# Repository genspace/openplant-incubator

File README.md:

# OpenPlant Incubator

The code in this repository is open sourced and provides tools to develop a plant incubator.We hope this repository can be used as a model to inspire similar work among other research teams.

ToDo: Update this https://trello.com/b/W0jccEJs/welcome-to-the-project

Complete block diagram is saved in the genspace/openplant google drive. See `Incubator functional block diagram`

Please feel free to get in touch with the team.

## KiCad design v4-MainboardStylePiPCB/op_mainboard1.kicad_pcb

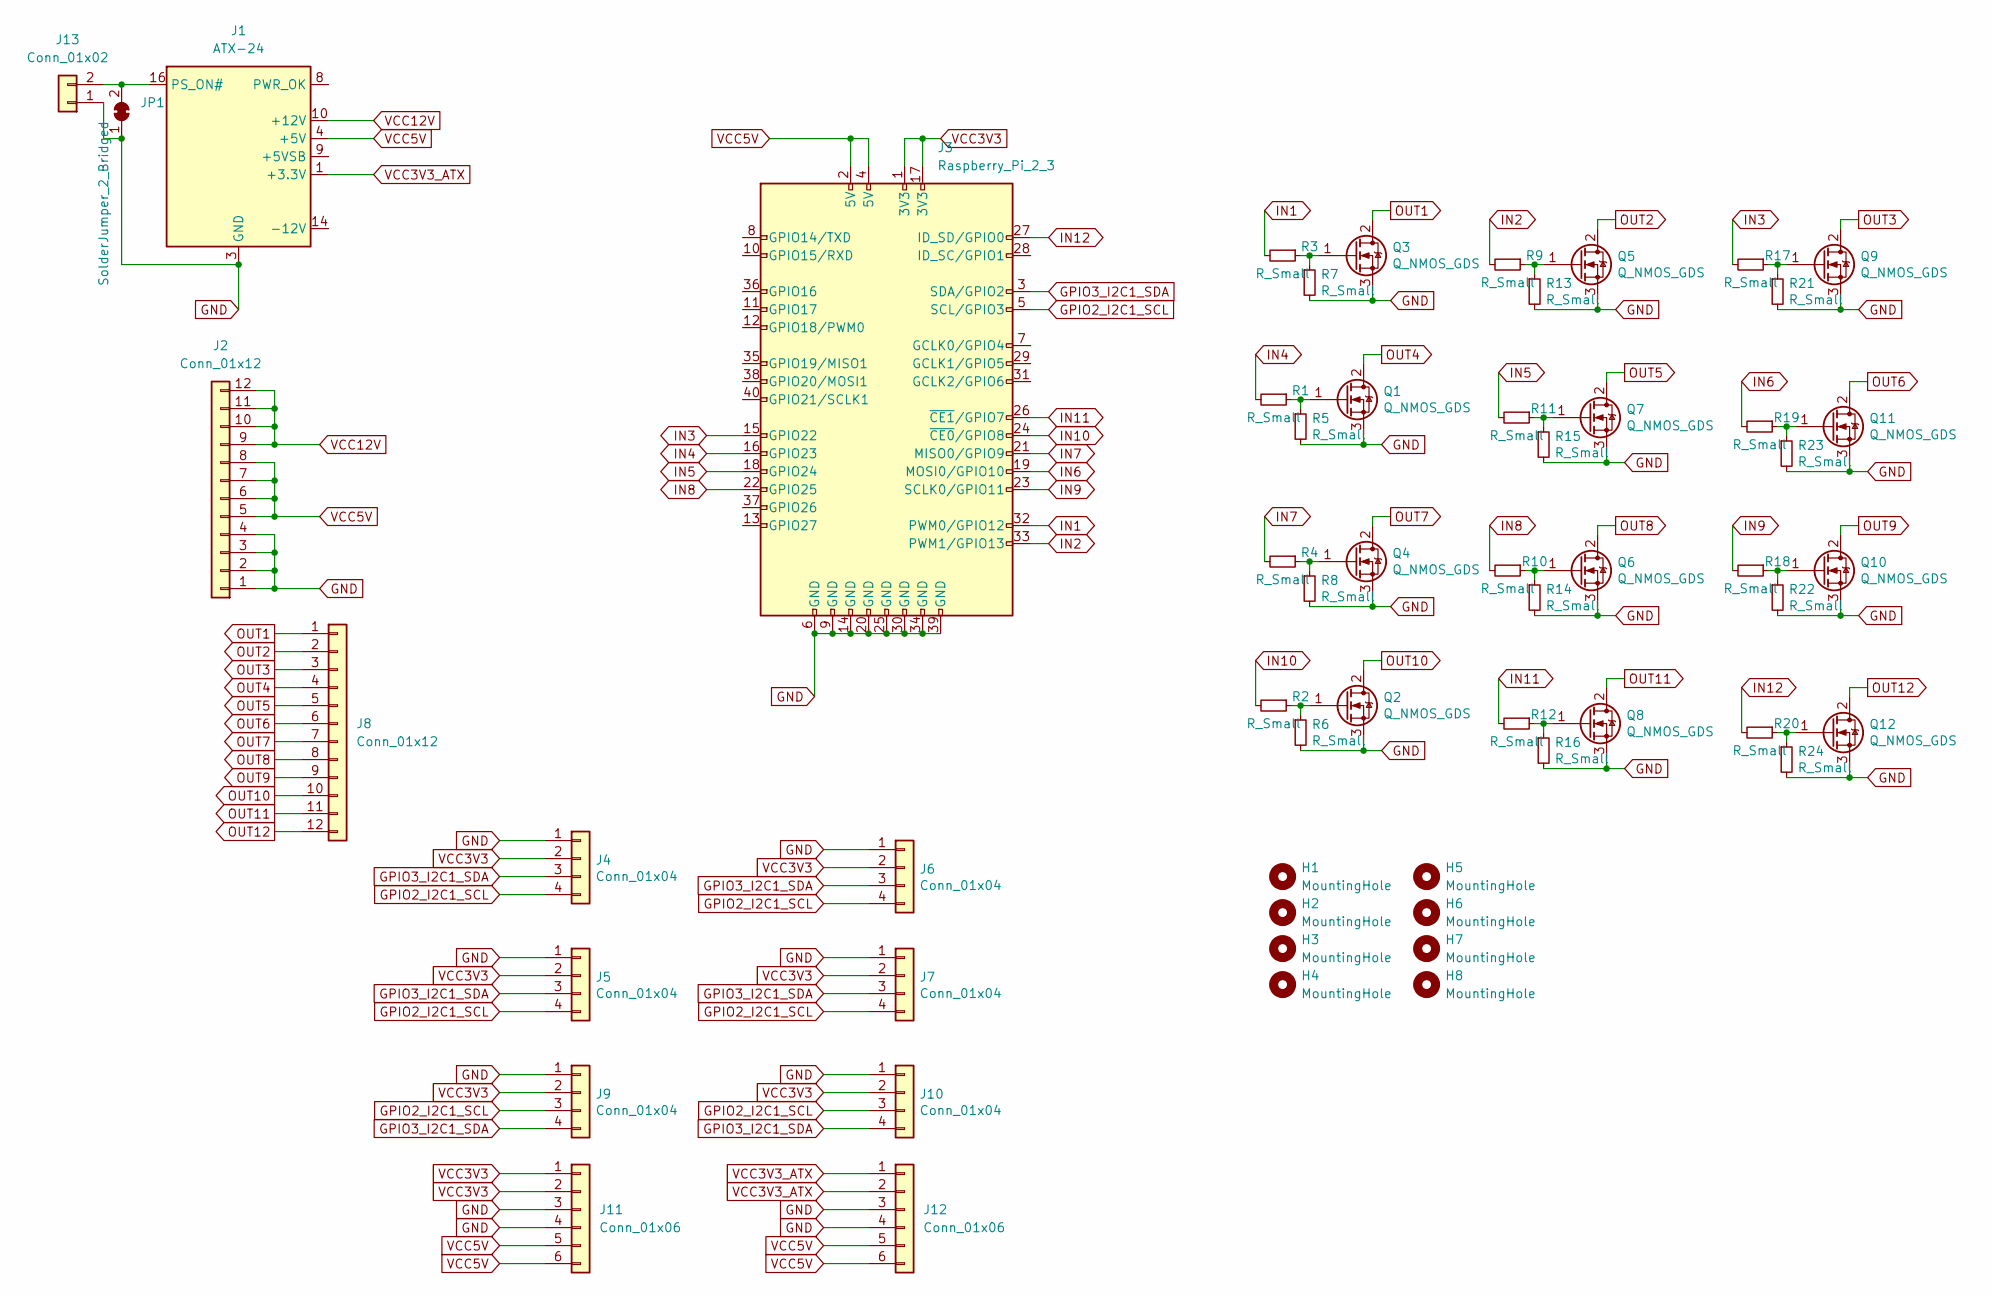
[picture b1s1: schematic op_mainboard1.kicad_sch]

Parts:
H1, H2, H3, H4, H5, H6, H7, H8: MountingHole; MountingHole_2.7mm_M2.5_KeepOuts
J1: ATX-24; Molex_Mini-Fit_Jr_5569-24A2_2x12_P4.20mm_Horizontal
J2, J8: Conn_01x12; Conn_01x12_P3.84_dbparts
J3: Raspberry_Pi_2_3; PinHeader_2x20_P2.54mm_Vertical
J4, J5, J6, J7: Conn_01x04; JST_SH_SM04B-SRSS-TB_1x04-1MP_P1.00mm_Horizontal
J9, J10: Conn_01x04; PinHeader_1x04_P2.54mm_Vertical
J11, J12: Conn_01x06; PinHeader_1x06_P2.54mm_Vertical
J13: Conn_01x02; PinHeader_1x02_P2.54mm_Vertical
JP1: SolderJumper_2_Bridged; SolderJumper-2_P1.3mm_Bridged_RoundedPad1.0x1.5mm
Q1, Q2, Q3, Q4, Q5, Q6, Q7, Q8, Q9, Q10, Q11, Q12: Q_NMOS_GDS; TO-252-2
R1, R2, R3, R4, R5, R6, R7, R8, R9, R10, R11, R12, R13, R14, R15, R16, R17, R18, R19, R20, R21, R22, R23, R24: R_Small; R_0805_2012Metric_Pad1.20x1.40mm_HandSolder

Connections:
GND: J1.3 (GND), J1.5 (GND), J1.7 (GND), J1.15 (GND), J1.17 (GND), J1.18 (GND), J1.19 (GND), J1.24 (GND), J2.1, J2.2, J2.3, J2.4, J3.6 (GND), J3.9 (GND), J3.14 (GND), J3.20 (GND), J3.25 (GND), J3.30 (GND), J3.34 (GND), J3.39 (GND), J4.1, J5.1, J6.1, J7.1, J9.1, J10.1, J11.3, J11.4, J12.3, J12.4, J13.1, JP1.1 (A), Q1.3 (S), Q2.3 (S), Q3.3 (S), Q4.3 (S), Q5.3 (S), Q6.3 (S), Q7.3 (S), Q8.3 (S), Q9.3 (S), Q10.3 (S), Q11.3 (S), Q12.3 (S), R5.2, R6.2, R7.2, R8.2, R13.2, R14.2, R15.2, R16.2, R21.2, R22.2, R23.2, R24.2
GPIO2_I2C1_SCL: J3.5 (SCL/GPIO3), J4.4, J5.4, J6.4, J7.4, J9.3, J10.3
GPIO3_I2C1_SDA: J3.3 (SDA/GPIO2), J4.3, J5.3, J6.3, J7.3, J9.4, J10.4
IN1: J3.32 (PWM0/GPIO12), R3.2
IN2: J3.33 (PWM1/GPIO13), R9.2
IN3: J3.15 (GPIO22), R17.2
IN4: J3.16 (GPIO23), R1.2
IN5: J3.18 (GPIO24), R11.2
IN6: J3.19 (MOSI0/GPIO10), R19.2
IN7: J3.21 (MISO0/GPIO9), R4.2
IN8: J3.22 (GPIO25), R10.2
IN9: J3.23 (SCLK0/GPIO11), R18.2
IN10: J3.24 (~CE0/GPIO8), R2.2
IN11: J3.26 (~CE1/GPIO7), R12.2
IN12: J3.27 (ID_SD/GPIO0), R20.2
unnamed: J1.16 (PS_ON#), J13.2, JP1.2 (B)
unnamed: Q1.1 (G), R1.1, R5.1
unnamed: Q2.1 (G), R2.1, R6.1
unnamed: Q3.1 (G), R3.1, R7.1
unnamed: Q4.1 (G), R4.1, R8.1
unnamed: Q5.1 (G), R9.1, R13.1
unnamed: Q6.1 (G), R10.1, R14.1
unnamed: Q7.1 (G), R11.1, R15.1
unnamed: Q8.1 (G), R12.1, R16.1
unnamed: Q9.1 (G), R17.1, R21.1
unnamed: Q10.1 (G), R18.1, R22.1
unnamed: Q11.1 (G), R19.1, R23.1
unnamed: Q12.1 (G), R20.1, R24.1
OUT1: J8.1, Q3.2 (D)
OUT2: J8.2, Q5.2 (D)
OUT3: J8.3, Q9.2 (D)
OUT4: J8.4, Q1.2 (D)
OUT5: J8.5, Q7.2 (D)
OUT6: J8.6, Q11.2 (D)
OUT7: J8.7, Q4.2 (D)
OUT8: J8.8, Q6.2 (D)
OUT9: J8.9, Q10.2 (D)
OUT10: J8.10, Q2.2 (D)
OUT11: J8.11, Q8.2 (D)
OUT12: J8.12, Q12.2 (D)
VCC3V3: J3.1 (3V3), J3.17 (3V3), J4.2, J5.2, J6.2, J7.2, J9.2, J10.2, J11.1, J11.2
VCC3V3_ATX: J1.1 (+3.3V), J1.2 (+3.3V), J1.12 (+3.3V), J1.13 (+3.3V), J12.1, J12.2
VCC5V: J1.4 (+5V), J1.6 (+5V), J1.21 (+5V), J1.22 (+5V), J1.23 (+5V), J2.5, J2.6, J2.7, J2.8, J3.2 (5V), J3.4 (5V), J11.5, J11.6, J12.5, J12.6
VCC12V: J1.10 (+12V), J1.11 (+12V), J2.9, J2.10, J2.11, J2.12

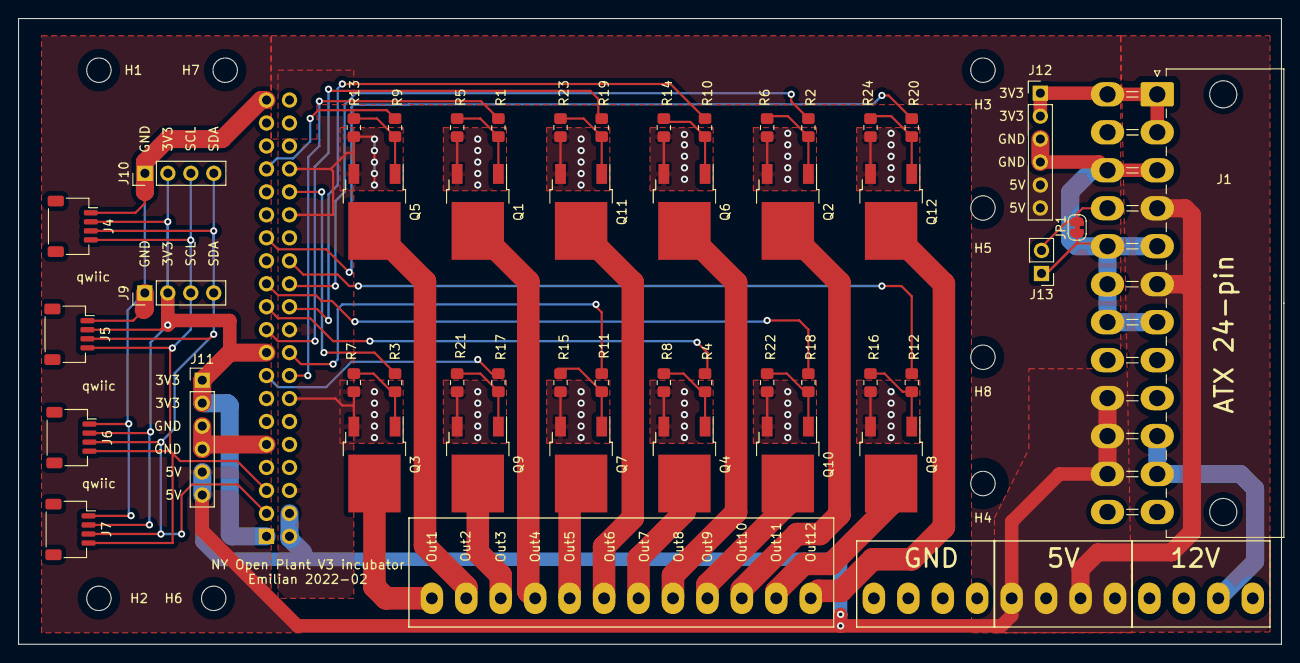
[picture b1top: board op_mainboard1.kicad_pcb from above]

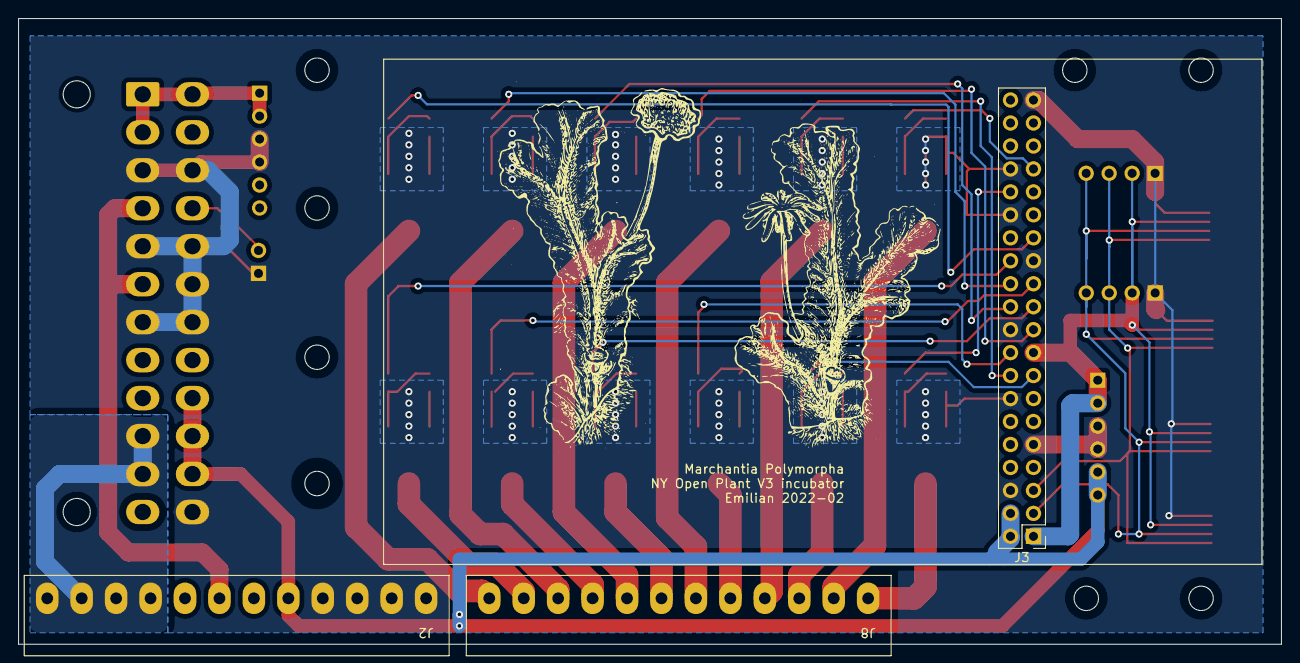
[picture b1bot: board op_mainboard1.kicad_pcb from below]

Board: 2 copper layers, 139.7 x 69.2 mm, 58 parts (3 on the bottom side), 44 nets.

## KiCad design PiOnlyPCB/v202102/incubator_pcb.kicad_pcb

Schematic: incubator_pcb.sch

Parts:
D1: LED; D_0805_2012Metric_Pad1.15x1.40mm_HandSolder
J1: Conn_01x05; PinHeader_1x05_P2.54mm_Vertical
J2: Conn_01x12_Female; PWRCON_3M81-12
J3: Conn_01x05_Female; PWRCON_3M81-5
J8: Conn_02x03_Odd_Even; PinHeader_2x03_P2.54mm_Vertical
R1: R_Small; R_0805_2012Metric_Pad1.20x1.40mm_HandSolder
U1: header_pi_zero_w; PinHeader_2x20_P2.54mm_Vertical

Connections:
/IN1: U1.32 (GPIO12_PWM0); also elsewhere on the board
/IN2: U1.33 (GPIO13_PWM1); also elsewhere on the board
/IN3: U1.15 (GPIO22); also elsewhere on the board
/IN4: U1.16 (GPIO23); also elsewhere on the board
/IN5: U1.18 (GPIO24); also elsewhere on the board
/IN6: U1.19 (GPIO10_MOSI); also elsewhere on the board
/IN7: U1.21 (GPIO9_MISO); also elsewhere on the board
/IN8: U1.22 (GPIO25); also elsewhere on the board
/IN9: U1.23 (GPIO11_SCLK); also elsewhere on the board
/IN10: U1.24 (GPIO8_CE0); also elsewhere on the board
/IN11: U1.26 (GPIO7_CE1); also elsewhere on the board
/IN12: U1.27 (GPIO0_ID_SC); also elsewhere on the board
/OUT1: J2.1; also elsewhere on the board
/OUT2: J2.2; also elsewhere on the board
/OUT3: J2.3; also elsewhere on the board
/OUT4: J2.4; also elsewhere on the board
/OUT5: J2.5; also elsewhere on the board
/OUT6: J2.6; also elsewhere on the board
/OUT7: J2.7; also elsewhere on the board
/OUT8: J2.8; also elsewhere on the board
/OUT9: J2.9; also elsewhere on the board
/OUT10: J2.10; also elsewhere on the board
/OUT11: J2.11; also elsewhere on the board
/OUT12: J2.12; also elsewhere on the board
ADL1: J8.1, U1.11 (GPIO17)
ADL2: J8.2, U1.12 (GPIO18_PWM0)
ADL3: J8.3, U1.13 (GPIO27)
ADL4: J8.4, U1.36 (GPIO16)
ADL5: J8.5, U1.37 (GPIO26)
ADL6: J8.6, U1.38 (GPIO20_SPI1_MOSI)
GND: J1.3, J3.1, J3.2, J3.3, J3.4, J3.5, R1.1, U1.6 (GND[8]), U1.9 (GND[8]), U1.14 (GND[8]), U1.20 (GND[8]), U1.25 (GND[8]), U1.30 (GND[8]), U1.34 (GND[8]), U1.39 (GND[8]); also elsewhere on the board
GPIO2_I2C1_SCL: U1.5 (GPIO3_I2C1_SCL); also elsewhere on the board
GPIO2_I2C1_SDA: U1.3 (GPIO2_I2C1_SDA); also elsewhere on the board
unnamed: D1.1 (K), R1.2
VCC3V3: D1.2 (A), J1.1, J1.2, U1.1 (VCC3V3), U1.17 (VCC3V3); also elsewhere on the board
VCC5V: J1.4, J1.5, U1.2 (VCC5V), U1.4 (VCC5V)

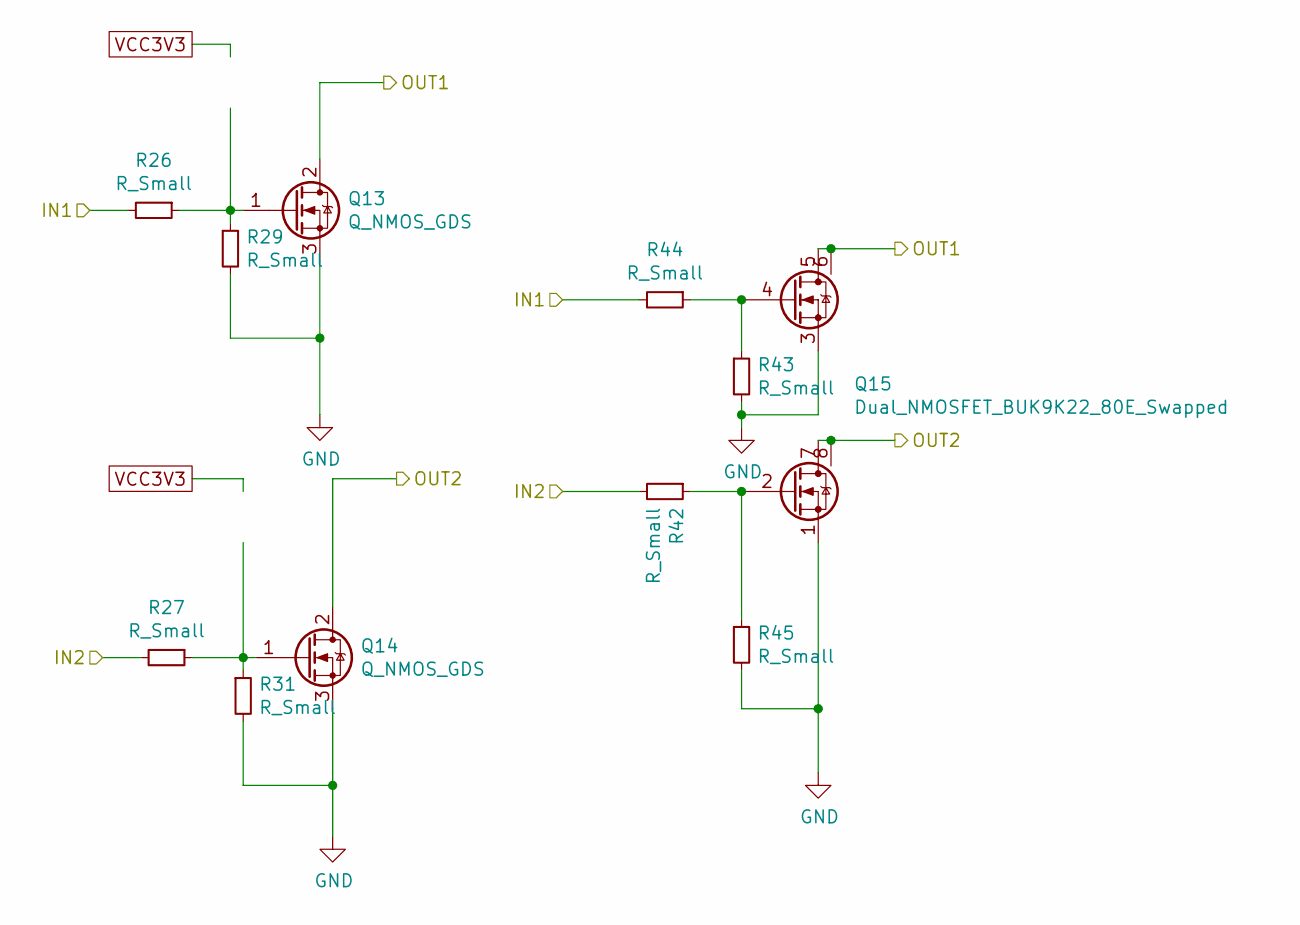
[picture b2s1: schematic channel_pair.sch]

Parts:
Q1, Q2: Q_NMOS_GDS; TO-252-2
Q3: Dual_NMOSFET_BUK9K22_80E_Swapped; LFPAK56D
R2, R3, R4, R5, R6, R7, R10, R12: R_Small; R_0805_2012Metric_Pad1.20x1.40mm_HandSolder

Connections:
/IN1: R2.2, R10.2; also elsewhere on the board
/IN2: R3.2, R4.2; also elsewhere on the board
/OUT1: Q1.2 (D), Q3.5 (D1), Q3.6 (D1); also elsewhere on the board
/OUT2: Q2.2 (D), Q3.7 (D2), Q3.8 (D2); also elsewhere on the board
GND: Q1.3 (S), Q2.3 (S), Q3.1 (S2), Q3.3 (S1), R5.2, R6.2, R7.2, R12.2; also elsewhere on the board
unnamed: Q1.1 (G), R2.1, R5.1
unnamed: Q2.1 (G), R3.1, R7.1
unnamed: Q3.2 (G2), R4.1, R12.1
unnamed: Q3.4 (G1), R6.1, R10.1

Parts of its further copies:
Q4, Q5, Q7, Q8, Q10, Q11, Q13, Q14, Q16, Q17: Q_NMOS_GDS; TO-252-2
Q6, Q9, Q12, Q15, Q18: Dual_NMOSFET_BUK9K22_80E_Swapped; LFPAK56D
R8, R9, R11, R13, R14, R15, R16, R17, R18, R19, R20, R21, R22, R23, R24, R25, R26, R27, R28, R29, R30, R31, R32, R33, R34, R35, R36, R37, R38, R39, R40, R41, R42, R43, R44, R45, R46, R47, R48, R49: R_Small; R_0805_2012Metric_Pad1.20x1.40mm_HandSolder

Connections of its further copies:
/IN3: R8.2, R22.2; also elsewhere on the board
/IN4: R9.2, R16.2; also elsewhere on the board
/IN5: R26.2, R44.2; also elsewhere on the board
/IN6: R27.2, R42.2; also elsewhere on the board
/IN7: R32.2, R48.2; also elsewhere on the board
/IN8: R33.2, R46.2; also elsewhere on the board
/IN9: R14.2, R34.2; also elsewhere on the board
/IN10: R15.2, R28.2; also elsewhere on the board
/IN11: R20.2, R40.2; also elsewhere on the board
/IN12: R21.2, R38.2; also elsewhere on the board
/OUT3: Q4.2 (D), Q6.5 (D1), Q6.6 (D1); also elsewhere on the board
/OUT4: Q5.2 (D), Q6.7 (D2), Q6.8 (D2); also elsewhere on the board
/OUT5: Q13.2 (D), Q15.5 (D1), Q15.6 (D1); also elsewhere on the board
/OUT6: Q14.2 (D), Q15.7 (D2), Q15.8 (D2); also elsewhere on the board
/OUT7: Q16.2 (D), Q18.5 (D1), Q18.6 (D1); also elsewhere on the board
/OUT8: Q17.2 (D), Q18.7 (D2), Q18.8 (D2); also elsewhere on the board
/OUT9: Q7.2 (D), Q9.5 (D1), Q9.6 (D1); also elsewhere on the board
/OUT10: Q8.2 (D), Q9.7 (D2), Q9.8 (D2); also elsewhere on the board
/OUT11: Q10.2 (D), Q12.5 (D1), Q12.6 (D1); also elsewhere on the board
/OUT12: Q11.2 (D), Q12.7 (D2), Q12.8 (D2); also elsewhere on the board
GND: Q4.3 (S), Q5.3 (S), Q6.1 (S2), Q6.3 (S1), Q7.3 (S), Q8.3 (S), Q9.1 (S2), Q9.3 (S1), Q10.3 (S), Q11.3 (S), Q12.1 (S2), Q12.3 (S1), Q13.3 (S), Q14.3 (S), Q15.1 (S2), Q15.3 (S1), Q16.3 (S), Q17.3 (S), Q18.1 (S2), Q18.3 (S1), R11.2, R13.2, R17.2, R18.2, R19.2, R23.2, R24.2, R25.2, R29.2, R30.2, R31.2, R35.2, R36.2, R37.2, R39.2, R41.2, R43.2, R45.2, R47.2, R49.2; also elsewhere on the board
unnamed: Q4.1 (G), R8.1, R11.1
unnamed: Q5.1 (G), R9.1, R13.1
unnamed: Q6.2 (G2), R16.1, R24.1
unnamed: Q6.4 (G1), R18.1, R22.1
unnamed: Q7.1 (G), R14.1, R17.1
unnamed: Q8.1 (G), R15.1, R19.1
unnamed: Q9.2 (G2), R28.1, R36.1
unnamed: Q9.4 (G1), R30.1, R34.1
unnamed: Q10.1 (G), R20.1, R23.1
unnamed: Q11.1 (G), R21.1, R25.1
unnamed: Q12.2 (G2), R38.1, R41.1
unnamed: Q12.4 (G1), R39.1, R40.1
unnamed: Q13.1 (G), R26.1, R29.1
unnamed: Q14.1 (G), R27.1, R31.1
unnamed: Q15.2 (G2), R42.1, R45.1
unnamed: Q15.4 (G1), R43.1, R44.1
unnamed: Q16.1 (G), R32.1, R35.1
unnamed: Q17.1 (G), R33.1, R37.1
unnamed: Q18.2 (G2), R46.1, R49.1
unnamed: Q18.4 (G1), R47.1, R48.1

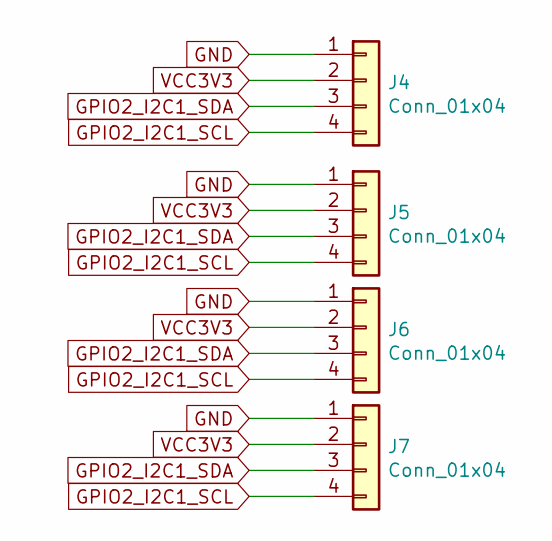
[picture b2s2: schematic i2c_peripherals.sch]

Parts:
J4, J5: Conn_01x04; JST_SH_BM04B-SRSS-TB_1x04-1MP_P1.00mm_Vertical
J6, J7: Conn_01x04; PinHeader_1x04_P2.54mm_Vertical

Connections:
GND: J4.1, J5.1, J6.1, J7.1; also elsewhere on the board
GPIO2_I2C1_SCL: J4.4, J5.4, J6.4, J7.4; also elsewhere on the board
GPIO2_I2C1_SDA: J4.3, J5.3, J6.3, J7.3; also elsewhere on the board
VCC3V3: J4.2, J5.2, J6.2, J7.2; also elsewhere on the board

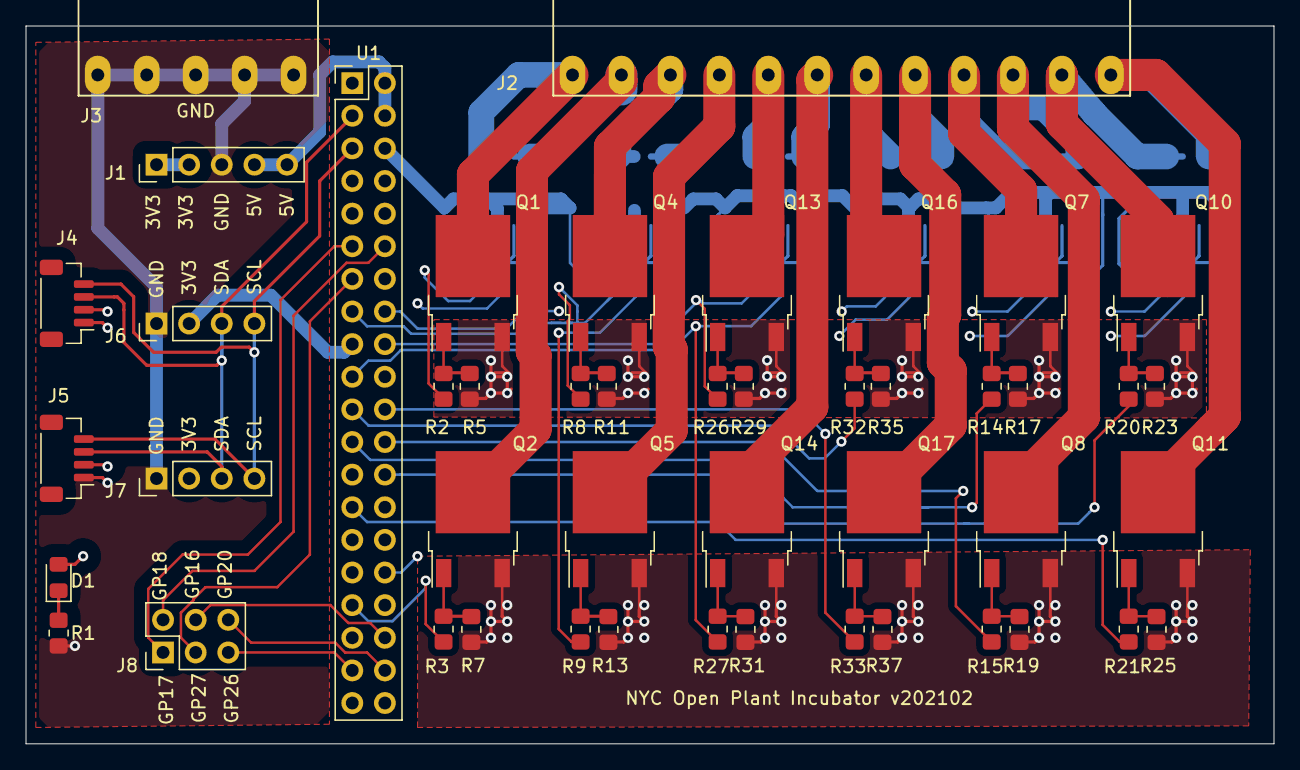
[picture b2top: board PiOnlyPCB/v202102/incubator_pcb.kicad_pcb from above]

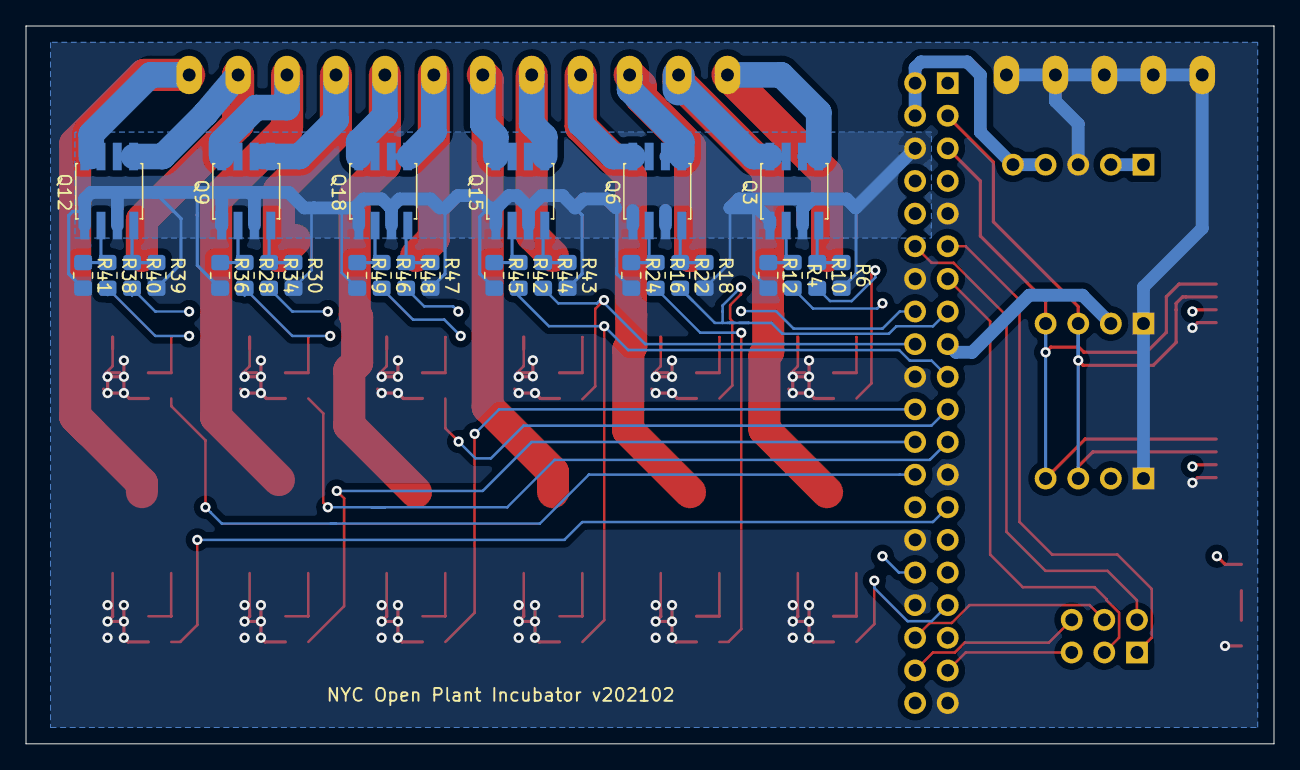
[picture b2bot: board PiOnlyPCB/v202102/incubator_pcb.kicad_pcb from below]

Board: 4 copper layers, 97.2 x 55.9 mm, 77 parts (30 on the bottom side), 60 nets.

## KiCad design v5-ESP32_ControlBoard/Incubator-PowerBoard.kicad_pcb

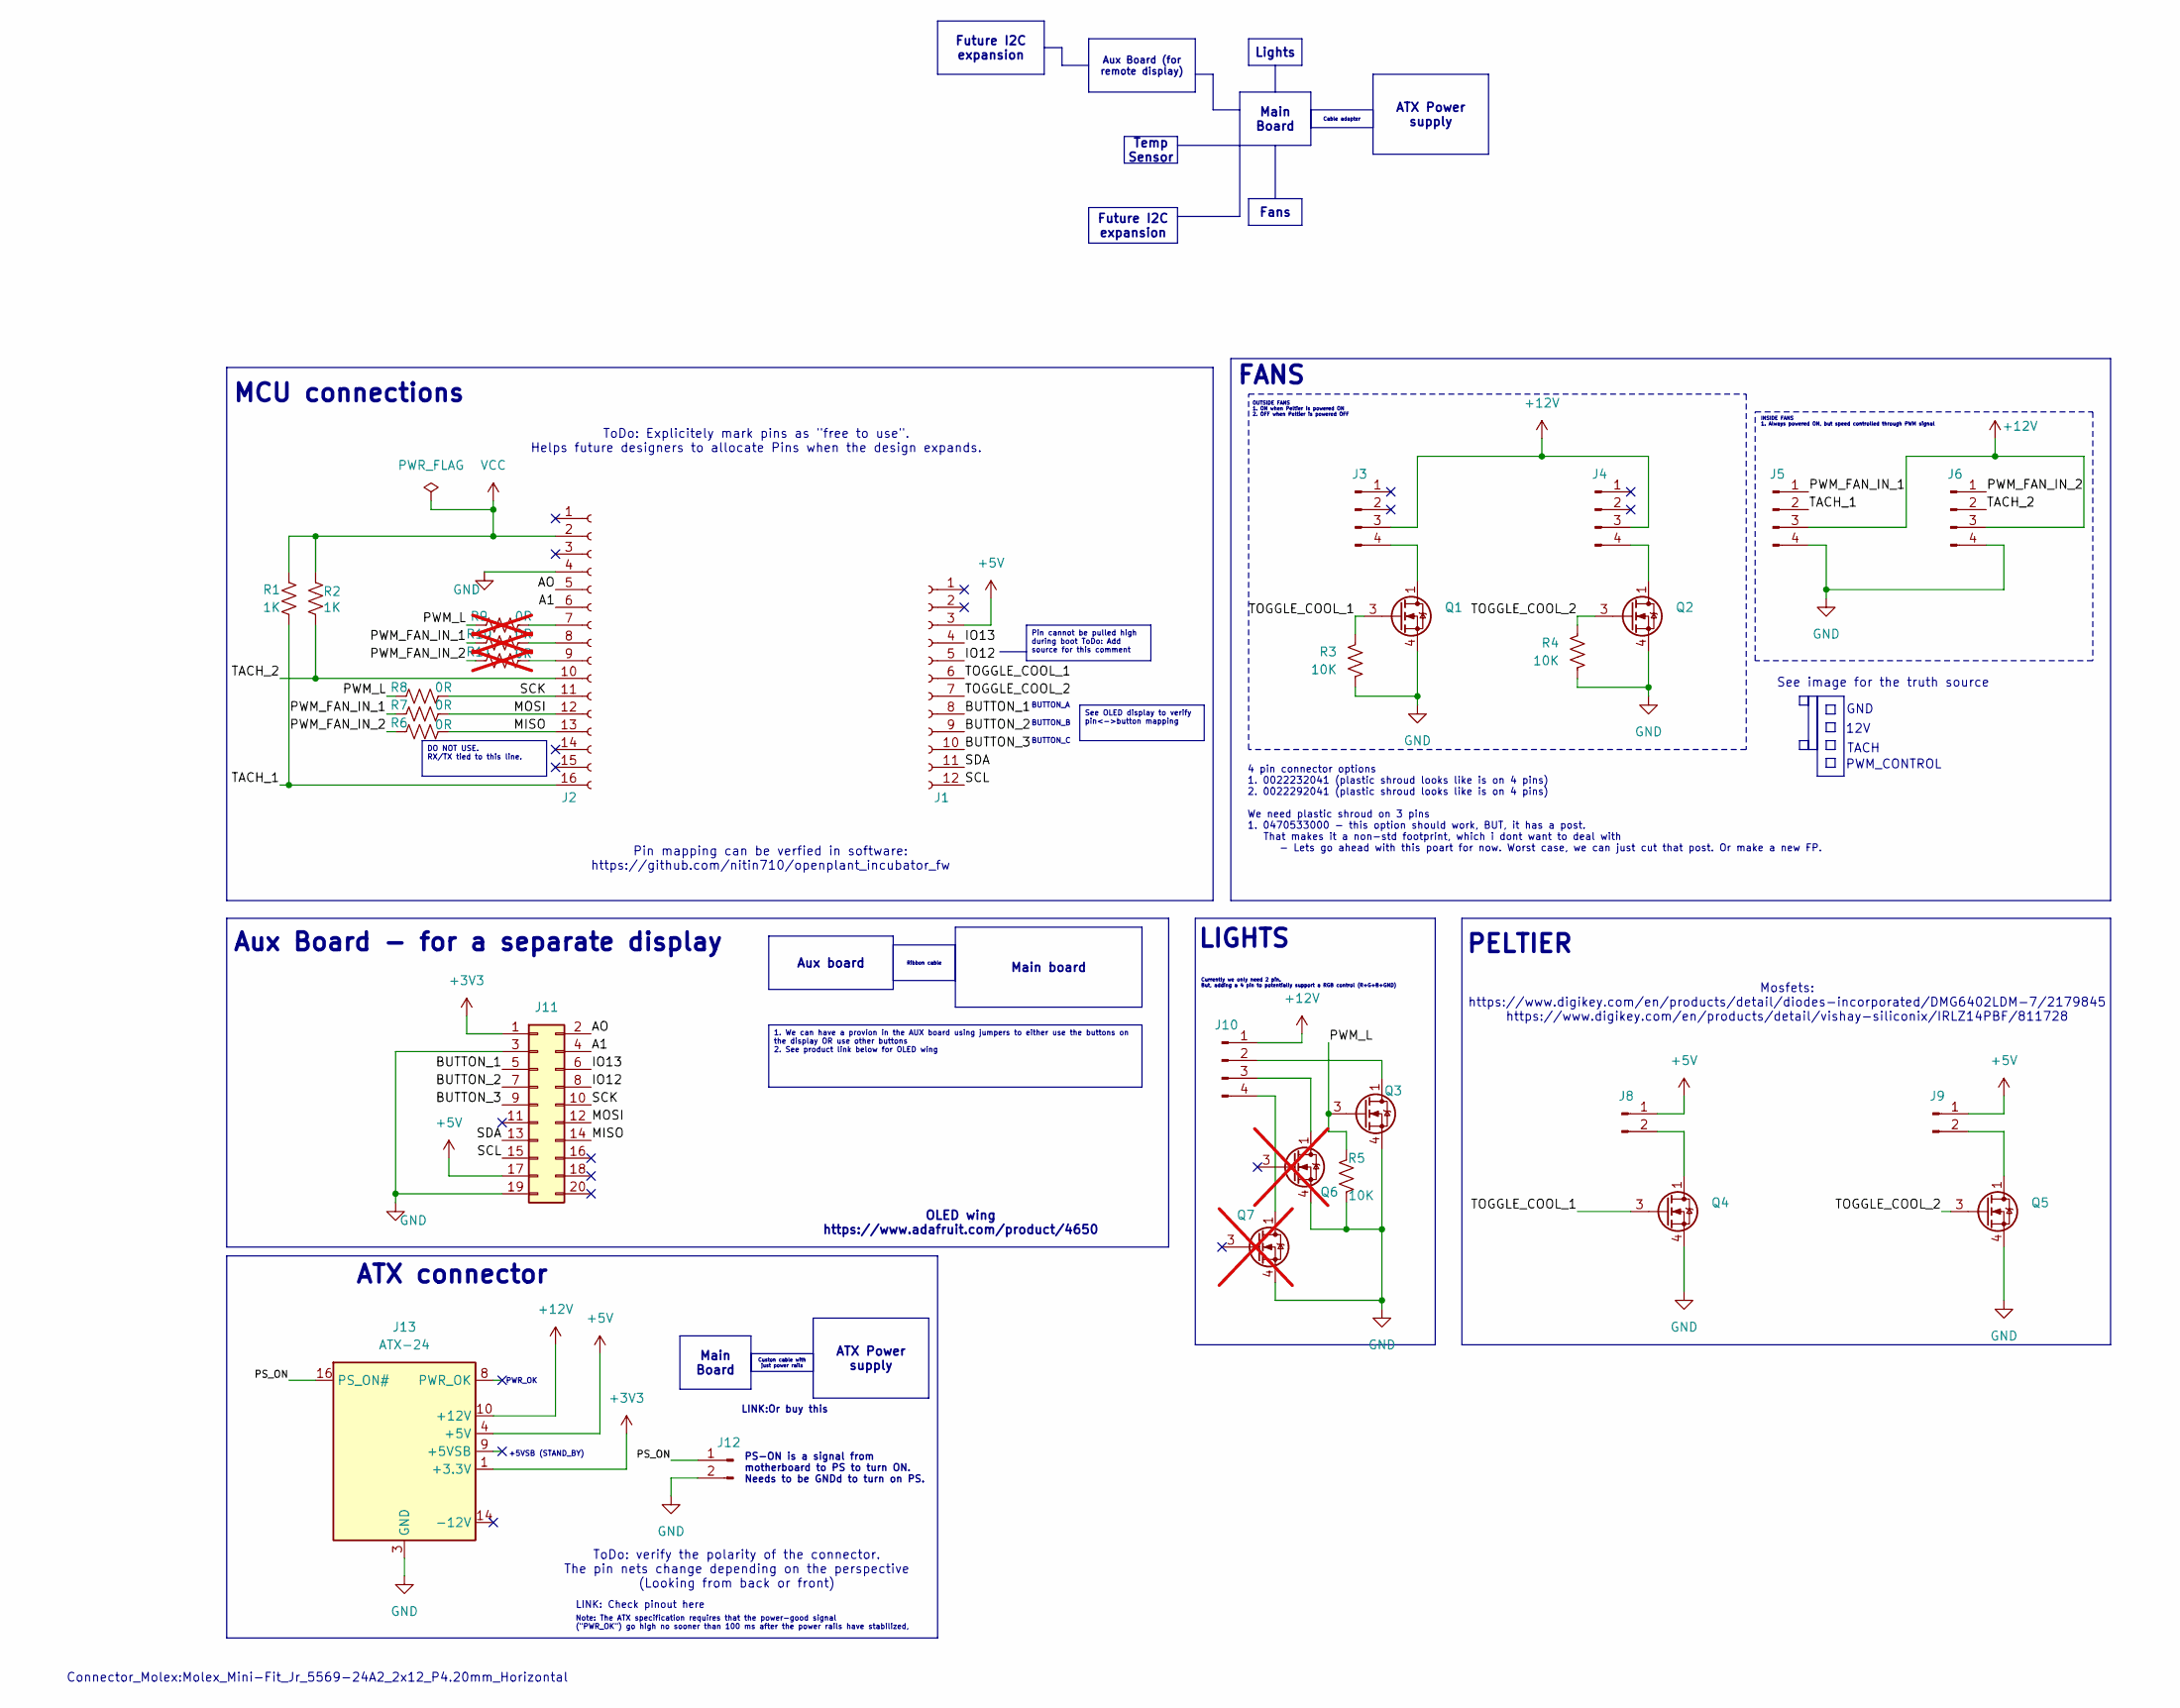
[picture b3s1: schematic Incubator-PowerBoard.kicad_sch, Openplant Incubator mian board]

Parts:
J1: Conn_01x12_Socket; PinSocket_1x12_P2.54mm_Vertical; MPN PPTC121LFBN-RC; Digikey_Part_Number S6100-ND
J2: Conn_01x16_Socket; PinSocket_1x16_P2.54mm_Vertical; MPN PPTC161LFBN-RC; Digikey_Part_Number S7014-ND
J3: OUT_FAN_1; PinHeader_1x04_P2.54mm_Vertical; MPN 61300411121; Digikey_Part_Number 732-5317-ND
J4: OUT_FAN_2; PinHeader_1x04_P2.54mm_Vertical; MPN 61300411121; Digikey_Part_Number 732-5317-ND
J5: IN_FAN_1; PinHeader_1x04_P2.54mm_Vertical; MPN 61300411121; Digikey_Part_Number 732-5317-ND
J6: IN_FAN_2; PinHeader_1x04_P2.54mm_Vertical; MPN 61300411121; Digikey_Part_Number 732-5317-ND
J8: PELTIER_1; PinHeader_1x02_P2.54mm_Vertical; MPN 61300211121; Digikey_Part_Number 732-5315-ND
J9: PELTIER_2; PinHeader_1x02_P2.54mm_Vertical; MPN 61300211121; Digikey_Part_Number 732-5315-ND
J10: LIGHTS; PinHeader_1x04_P2.54mm_Vertical; MPN 61300411121; Digikey_Part_Number 732-5317-ND
J11: Conn_02x10_Odd_Even; PinHeader_2x10_P2.54mm_Vertical
J12: Conn_01x02_Pin; PinHeader_1x02_P2.54mm_Vertical; MPN 61300211121; Digikey_Part_Number 732-5315-ND
J13: ATX-24; Molex_Mini-Fit_Jr_5569-24A2_2x12_P4.20mm_Horizontal
Q1: OUT_FAN_1; SOT-23-6; MPN DMG6402LVT-7; Digikey_Part_Number DMG6402LVT-7DICT-ND
Q2: OUT_FAN_2; SOT-23-6; MPN DMG6402LVT-7; Digikey_Part_Number DMG6402LVT-7DICT-ND
Q3: LIGHTS; SOT-23-6; MPN DMG6402LVT-7; Digikey_Part_Number DMG6402LVT-7DICT-ND
Q4: PELTIER_1; SOT-23-6; MPN DMG6402LVT-7; Digikey_Part_Number DMG6402LVT-7DICT-ND
Q5: PELTIER_2; SOT-23-6; MPN DMG6402LVT-7; Digikey_Part_Number DMG6402LVT-7DICT-ND
Q6, Q7: DMG6402LVT-7; SOT-23-6; MPN DMG6402LVT-7; Digikey_Part_Number DMG6402LVT-7DICT-ND; not fitted
R1, R2: 1K; R_1210_3225Metric; MPN CRCW12101K00JNEAIF
R3, R4, R5: 10K; R_0603_1608Metric; MPN RMCF0603JT10K0; Digikey_Part_Number RMCF0603JT10K0CT-ND
R6, R7, R8: 0R; R_0603_1608Metric; MPN RMCF0603ZT0R00; Digikey_Part_Number RMCF0603ZT0R00CT-ND
R9, R10, R11: 0R; R_0603_1608Metric; MPN RMCF0603ZT0R00; Digikey_Part_Number RMCF0603ZT0R00CT-ND; not fitted

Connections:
+3V3: J11.1, J13.1 (+3.3V), J13.2 (+3.3V), J13.12 (+3.3V), J13.13 (+3.3V)
+5V: J1.3, J8.1, J9.1, J11.17, J13.4 (+5V), J13.6 (+5V), J13.21 (+5V), J13.22 (+5V), J13.23 (+5V)
+12V: J3.3, J4.3, J5.3, J6.3, J10.1, J13.10 (+12V), J13.11 (+12V)
/A1: J2.6, J11.4
/AO: J2.5, J11.2
/BUTTON_1: J1.8, J11.5
/BUTTON_2: J1.9, J11.7
/BUTTON_3: J1.10, J11.9
/IO12: J1.5, J11.8
/IO13: J1.4, J11.6
/MISO: J2.13, J11.14, R6.2
/MOSI: J2.12, J11.12, R7.2
/PS_ON: J12.1, J13.16 (PS_ON#)
/PWM_FAN_IN_1: J5.1, R7.1, R10.1
/PWM_FAN_IN_2: J6.1, R6.1, R11.1
/PWM_L: Q3.3 (G), R5.1, R8.1, R9.1
/SCK: J2.11, J11.10, R8.2
/SCL: J1.12, J11.15
/SDA: J1.11, J11.13
/TACH_1: J2.16, J5.2, R1.2
/TACH_2: J2.10, J6.2, R2.2
/TOGGLE_COOL_1: J1.6, Q1.3 (G), Q4.3 (G), R3.1
/TOGGLE_COOL_2: J1.7, Q2.3 (G), Q5.3 (G), R4.1
GND: J2.4, J5.4, J6.4, J11.3, J11.19, J12.2, J13.3 (GND), J13.5 (GND), J13.7 (GND), J13.15 (GND), J13.17 (GND), J13.18 (GND), J13.19 (GND), J13.24 (GND), Q1.4 (S), Q2.4 (S), Q3.4 (S), Q4.4 (S), Q5.4 (S), Q6.4 (S), Q7.4 (S), R3.2, R4.2, R5.2
unnamed: J2.7, R9.2
unnamed: J2.8, R10.2
unnamed: J2.9, R11.2
unnamed: J3.4, Q1.1 (D), Q1.2 (D), Q1.5 (D), Q1.6 (D)
unnamed: J4.4, Q2.1 (D), Q2.2 (D), Q2.5 (D), Q2.6 (D)
unnamed: J8.2, Q4.1 (D), Q4.2 (D), Q4.5 (D), Q4.6 (D)
unnamed: J9.2, Q5.1 (D), Q5.2 (D), Q5.5 (D), Q5.6 (D)
unnamed: J10.2, Q3.1 (D), Q3.2 (D), Q3.5 (D), Q3.6 (D)
unnamed: J10.3, Q6.1 (D), Q6.2 (D), Q6.5 (D), Q6.6 (D)
unnamed: J10.4, Q7.1 (D), Q7.2 (D), Q7.5 (D), Q7.6 (D)
VCC: J2.2, R1.1, R2.1

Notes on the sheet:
Aux Board (for remote display)
Fans
ATX Power supply
DO NOT USE. RX/TX tied to this line.
See OLED display to verify pin<->button mapping
Main board
Cable adapter
Pin cannot be pulled high during boot ToDo: Add source for this comment
Lights
Future I2C expansion
Main Board
1. We can have a provion in the AUX board using jumpers to either use the buttons on the display OR use other buttons 2. See product link below for OLED wing
Ribbon cable
Custon cable with just power rails
Temp Sensor
Aux board
PELTIER
PWM_CONTROL
LINK:Or buy this
BUTTON_B
See image for the truth source
Aux Board - for a separate display
MCU connections
LINK: Check pinout here
4 pin connector options 1. 0022232041 (plastic shroud looks like is on 4 pins) 2. 0022292041 (plastic shroud looks like is on 4 pins) We need plastic shroud on 3 pins 1. 0470533000 - this option should work, BUT, it has a post. That makes it a non-std footprint, which i dont want to deal with - Let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
GND
Mosfets: https://www.digikey.com/en/products/detail/diodes-incorporated/DMG6402LDM-7/2179845 https://www.digikey.com/en/products/detail/vishay-siliconix/IRLZ14PBF/811728
BUTTON_C
ToDo: Explicitely mark pins as "free to use". Helps future designers to allocate Pins when the design expands.
OUTSIDE FANS 1. ON when Peltier is powered ON 2. OFF when Peltier is powered OFF
OLED wing https://www.adafruit.com/product/4650
Currently we only need 2 pin. But, adding a 4 pin to potentially support a RGB control (R+G+B+GND)
ATX connector
INSIDE FANS 1. Always powered ON, but speed controlled through PWM signal
Pin mapping can be verfied in software: https://github.com/nitin710/openplant_incubator_fw
ToDo: verify the polarity of the connector. The pin nets change depending on the perspective (Looking from back or front)
LIGHTS
+5VSB (STAND_BY)
BUTTON_A
FANS

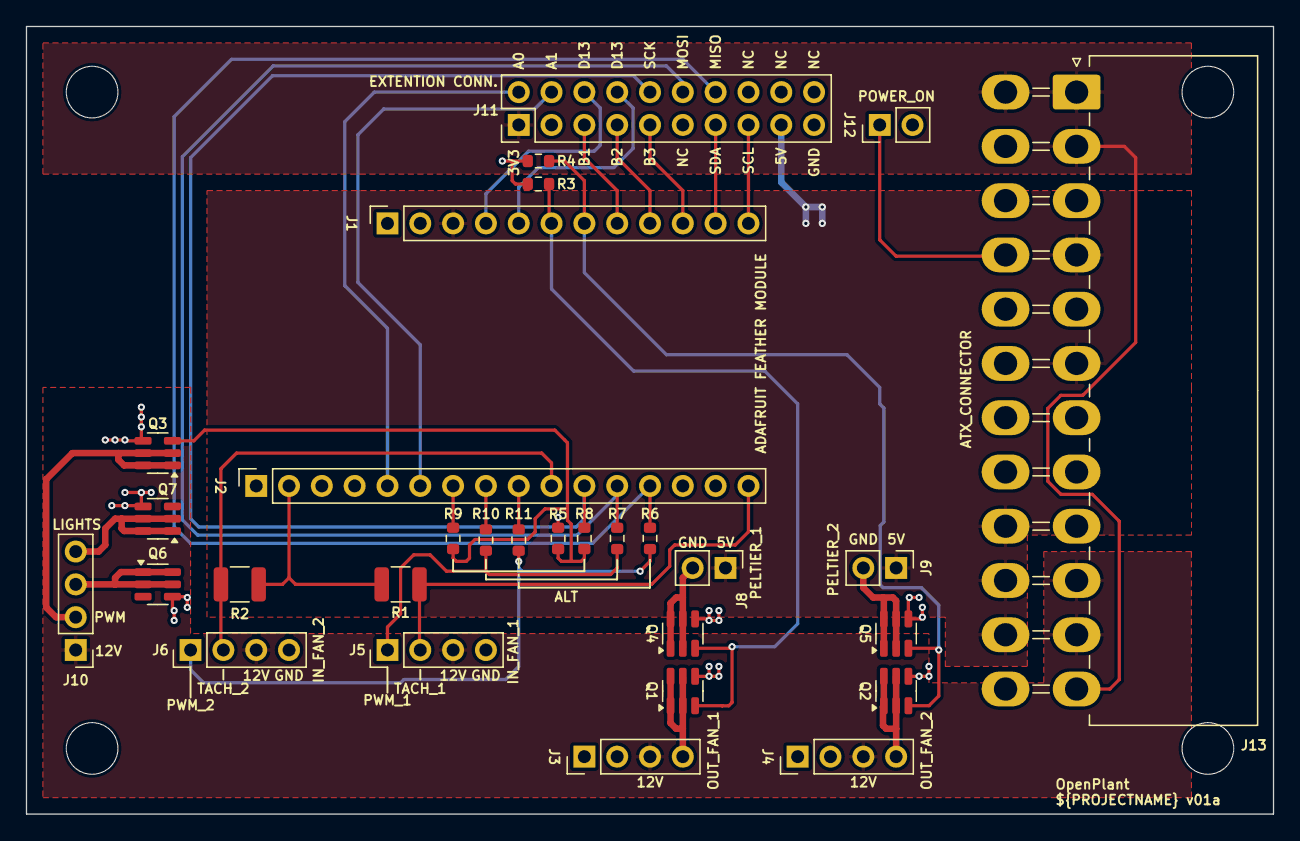
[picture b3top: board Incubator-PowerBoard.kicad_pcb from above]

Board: 2 copper layers, 96.5 x 61.0 mm, 30 parts (0 on the bottom side), 35 nets.

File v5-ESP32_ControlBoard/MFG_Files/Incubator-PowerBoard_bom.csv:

Component,Description,Part,References,Quantity Per PCB,Datasheet,Value,Footprint,MPN,Digikey_Part_Number
1,ATX Power supply 24pins,ATX-24,J13,1,https://www.intel.com/content/dam/www/public/us/en/documents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,ATX-24,Molex_Mini-Fit_Jr_5569-24A2_2x12_P4.20mm_Horizontal,,
2,CONN HDR 12POS 0.1 TIN PCB,Conn_01x12_Socket,J1,1,https://mm.digikey.com/Volume0/opasdata/d220001/medias/docus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,Conn_01x12_Socket,PinSocket_1x12_P2.54mm_Vertical,PPTC121LFBN-RC,S6100-ND
3,CONN HDR 16POS 0.1 TIN PCB,Conn_01x16_Socket,J2,1,https://mm.digikey.com/Volume0/opasdata/d220001/medias/docus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,Conn_01x16_Socket,PinSocket_1x16_P2.54mm_Vertical,PPTC161LFBN-RC,S7014-ND
4,"Generic connector, double row, 02x10, odd/even pin numbering scheme (row 1 odd numbers, row 2 even numbers), script generated (kicad-library-utils/schlib/autogen/connector/)",Conn_02x10_Odd_Even,J11,1,~,Conn_02x10_Odd_Even,PinHeader_2x10_P2.54mm_Vertical,,
5,CONN HEADER VERT 4POS 2.54MM,Conn_01x04_Pin,J3 J4 J5 J6 J10,5,https://www.we-online.com/components/products/datasheet/6130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,OUT_FAN_1,PinHeader_1x04_P2.54mm_Vertical,61300411121,732-5317-ND
6,CONN HEADER VERT 2POS 2.54MM,Conn_01x02_Pin,J8 J9 J12,3,https://www.we-online.com/components/products/datasheet/6130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,PELTIER_1,PinHeader_1x02_P2.54mm_Vertical,61300211121,732-5315-ND
7,MOSFET N-CH 30V 6A TSOT26,2N7002E_1,Q1 Q2 Q3 Q4 Q5,5,https://www.diodes.com/assets/Datasheets/DMG6402LVT.pdf,OUT_FAN_1,SOT-23-6,DMG6402LVT-7,DMG6402LVT-7DICT-ND
8,RES 0 OHM JUMPER 1/10W 0603,R_US,R6 R7 R8,3,https://www.seielect.com/catalog/sei-rmcf_rmcp.pdf,0R,R_0603_1608Metric,RMCF0603ZT0R00,RMCF0603ZT0R00CT-ND
9,Thick Film Resistors CRCW1210-IF 200 1K0 5% ET1 E3,R_US,R1 R2,2,https://www.vishay.com/doc?20024,1K,R_1210_3225Metric,CRCW12101K00JNEAIF,
10,RES 10K OHM 5% 1/10W 0603,R_US,R3 R4 R5,3,https://www.seielect.com/catalog/sei-rmcf_rmcp.pdf,10K,R_0603_1608Metric,RMCF0603JT10K0,RMCF0603JT10K0CT-ND





Component Groups:,12
Component Count:,30
Fitted Components:,25
Number of PCBs:,1
Total components:,25
Schematic Version:,v01a
Schematic Date:,2024-07-20
PCB Variant:,default
BoM Date:,2024-11-21T12:36:54-0500
Schematic Source:,Incubator-PowerBoard.kicad_sch
KiCad Version:,Eeschema 8.0.2
